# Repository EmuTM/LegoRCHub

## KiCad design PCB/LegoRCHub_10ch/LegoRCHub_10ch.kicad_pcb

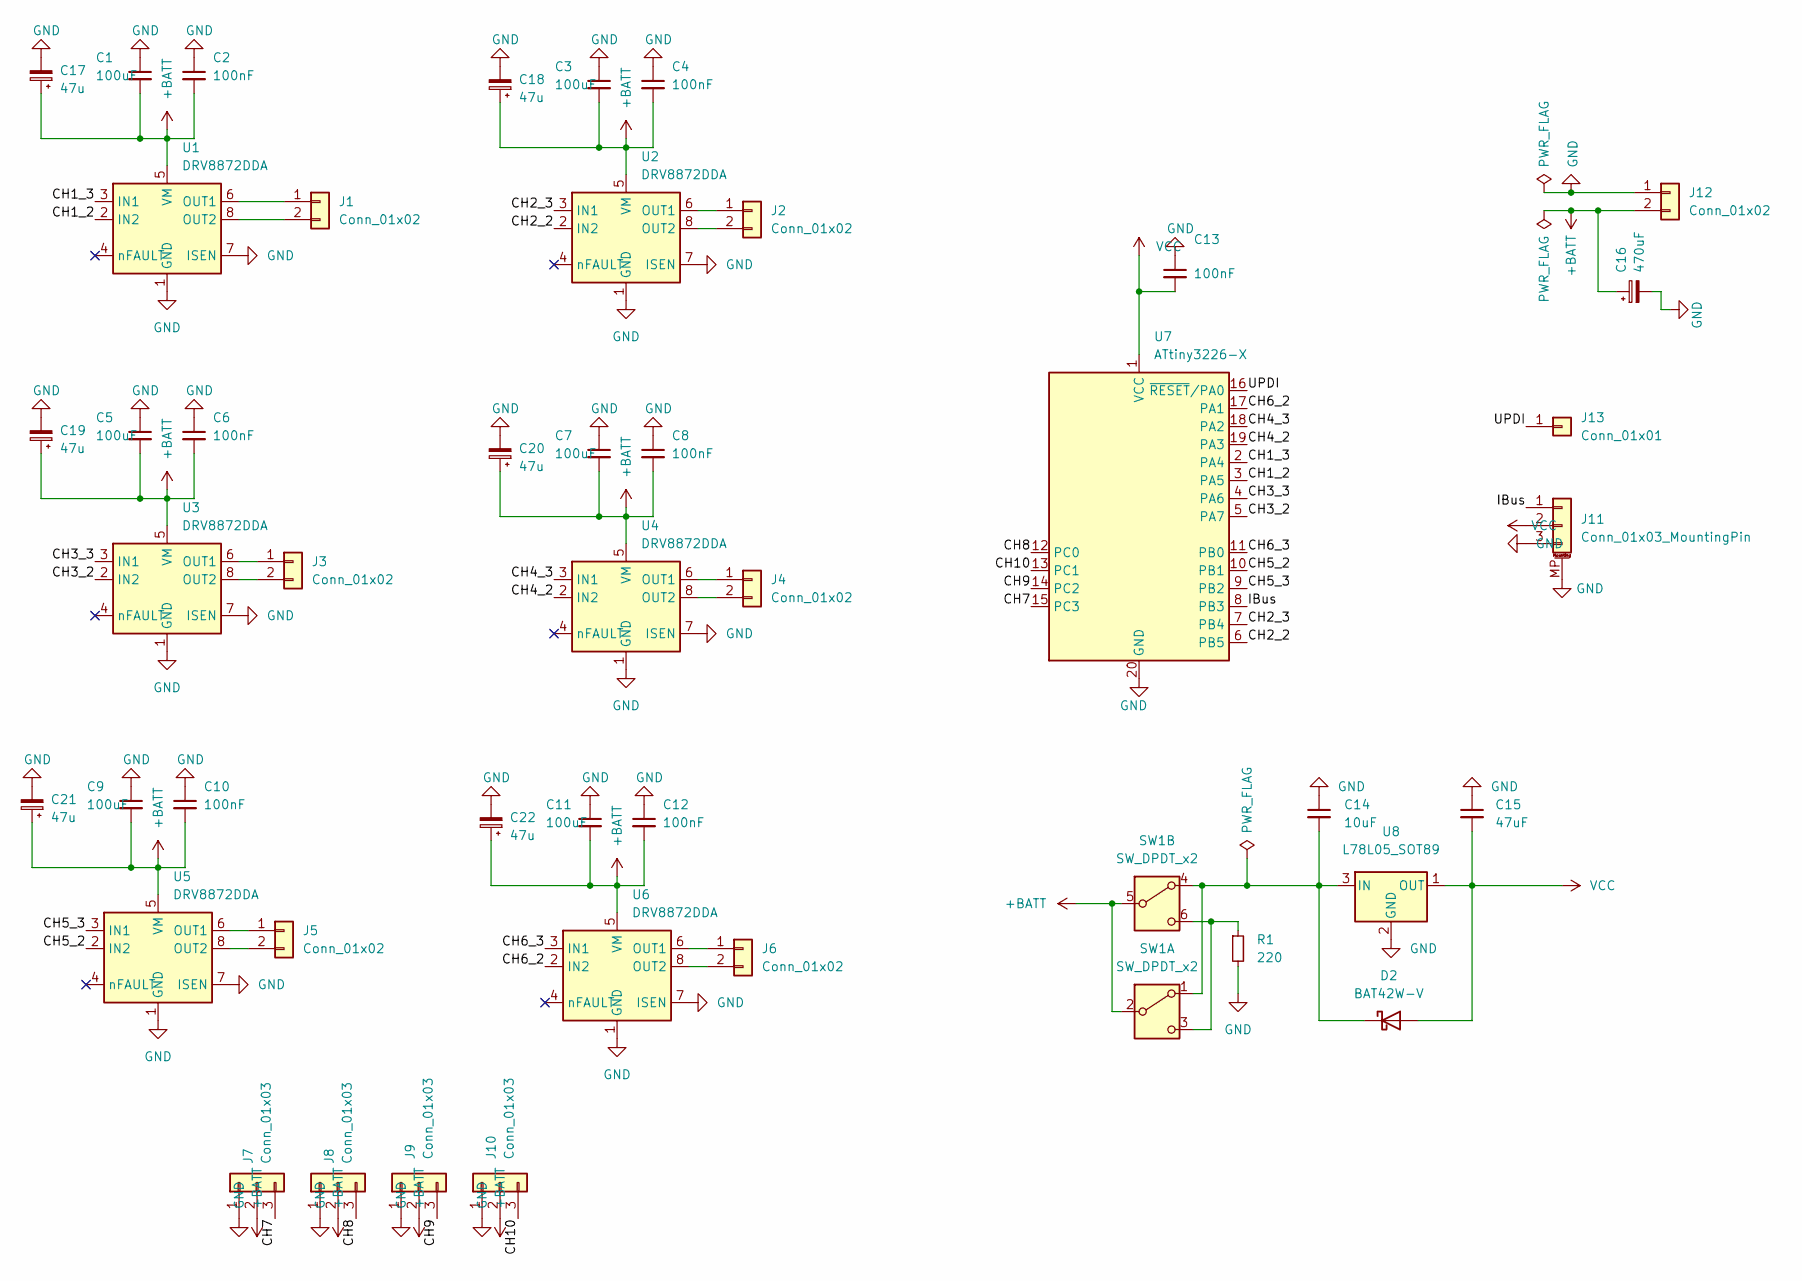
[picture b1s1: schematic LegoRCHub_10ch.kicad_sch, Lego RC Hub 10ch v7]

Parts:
C1, C3, C5, C7, C9, C11: 100uF; C_1206_3216Metric_Pad1.33x1.80mm_HandSolder
C2, C4, C6, C8, C10, C12: 100nF; C_0805_2012Metric_Pad1.18x1.45mm_HandSolder
C13: 100nF; C_1206_3216Metric_Pad1.33x1.80mm_HandSolder
C14: 10uF; C_0805_2012Metric_Pad1.18x1.45mm_HandSolder
C15: 47uF; C_0805_2012Metric_Pad1.18x1.45mm_HandSolder
C16: 470uF; CP_Elec_8x10.5
C17, C18, C19, C20, C21, C22: 47u; CP_Elec_5x5.4
D2: BAT42W-V; D_SOD-123
J1, J2, J3, J4, J5, J6: Conn_01x02; Molex_KK-254_AE-6410-02A_1x02_P2.54mm_Vertical
J7, J8, J9, J10: Conn_01x03; PinHeader_1x03_P2.54mm_Vertical
J11: Conn_01x03_MountingPin; JST_SH_BM03B-SRSS-TB_1x03-1MP_P1.00mm_Vertical
J12: Conn_01x02; AMASS_XT30U-M_1x02_P5.0mm_Vertical
J13: Conn_01x01; SolderWirePad_1x01_SMD_1x2mm
R1: 220; R_0805_2012Metric_Pad1.20x1.40mm_HandSolder
SW1: SW_DPDT_x2
U1, U2, U3, U4, U5, U6: DRV8872DDA; Texas_HTSOP-8-1EP_3.9x4.9mm_P1.27mm_EP2.95x4.9mm_Mask2.4x3.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
U7: ATtiny3226-X; SSOP-20_5.3x7.2mm_P0.65mm
U8: L78L05_SOT89; SOT-89-3

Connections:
+BATT: C1.2, C2.2, C3.2, C4.2, C5.2, C6.2, C7.2, C8.2, C9.2, C10.2, C11.2, C12.2, C16.1, C17.1, C18.1, C19.1, C20.1, C21.1, C22.1, J7.2, J8.2, J9.2, J10.2, J12.2, SW1.2 (B), SW1.5 (B), U1.5 (VM), U2.5 (VM), U3.5 (VM), U4.5 (VM), U5.5 (VM), U6.5 (VM)
/CH1_2: U1.2 (IN2), U7.3 (PA5)
/CH1_3: U1.3 (IN1), U7.2 (PA4)
/CH2_2: U2.2 (IN2), U7.6 (PB5)
/CH2_3: U2.3 (IN1), U7.7 (PB4)
/CH3_2: U3.2 (IN2), U7.5 (PA7)
/CH3_3: U3.3 (IN1), U7.4 (PA6)
/CH4_2: U4.2 (IN2), U7.19 (PA3)
/CH4_3: U4.3 (IN1), U7.18 (PA2)
/CH5_2: U5.2 (IN2), U7.10 (PB1)
/CH5_3: U5.3 (IN1), U7.9 (PB2)
/CH6_2: U6.2 (IN2), U7.17 (PA1)
/CH6_3: U6.3 (IN1), U7.11 (PB0)
/CH7: J7.3, U7.15 (PC3)
/CH8: J8.3, U7.12 (PC0)
/CH9: J9.3, U7.14 (PC2)
/CH10: J10.3, U7.13 (PC1)
/IBus: J11.1, U7.8 (PB3)
/UPDI: J13.1, U7.16 (~RESET/PA0)
GND: C1.1, C2.1, C3.1, C4.1, C5.1, C6.1, C7.1, C8.1, C9.1, C10.1, C11.1, C12.1, C13.1, C14.1, C15.1, C16.2, C17.2, C18.2, C19.2, C20.2, C21.2, C22.2, J7.1, J8.1, J9.1, J10.1, J11.3, J11.MP (MountPin), J12.1, R1.2, U1.1 (GND), U1.7 (ISEN), U1.9 (GND), U2.1 (GND), U2.7 (ISEN), U2.9 (GND), U3.1 (GND), U3.7 (ISEN), U3.9 (GND), U4.1 (GND), U4.7 (ISEN), U4.9 (GND), U5.1 (GND), U5.7 (ISEN), U5.9 (GND), U6.1 (GND), U6.7 (ISEN), U6.9 (GND), U7.20 (GND), U8.2 (GND)
unnamed: C14.2, D2.1 (K), SW1.1 (A), SW1.4 (A), U8.3 (IN)
unnamed: J1.1, U1.6 (OUT1)
unnamed: J1.2, U1.8 (OUT2)
unnamed: J2.1, U2.6 (OUT1)
unnamed: J2.2, U2.8 (OUT2)
unnamed: J3.1, U3.6 (OUT1)
unnamed: J3.2, U3.8 (OUT2)
unnamed: J4.1, U4.6 (OUT1)
unnamed: J4.2, U4.8 (OUT2)
unnamed: J5.1, U5.6 (OUT1)
unnamed: J5.2, U5.8 (OUT2)
unnamed: J6.1, U6.6 (OUT1)
unnamed: J6.2, U6.8 (OUT2)
unnamed: R1.1, SW1.3 (C), SW1.6 (C)
VCC: C13.2, C15.2, D2.2 (A), J11.2, U7.1 (VCC), U8.1 (OUT)

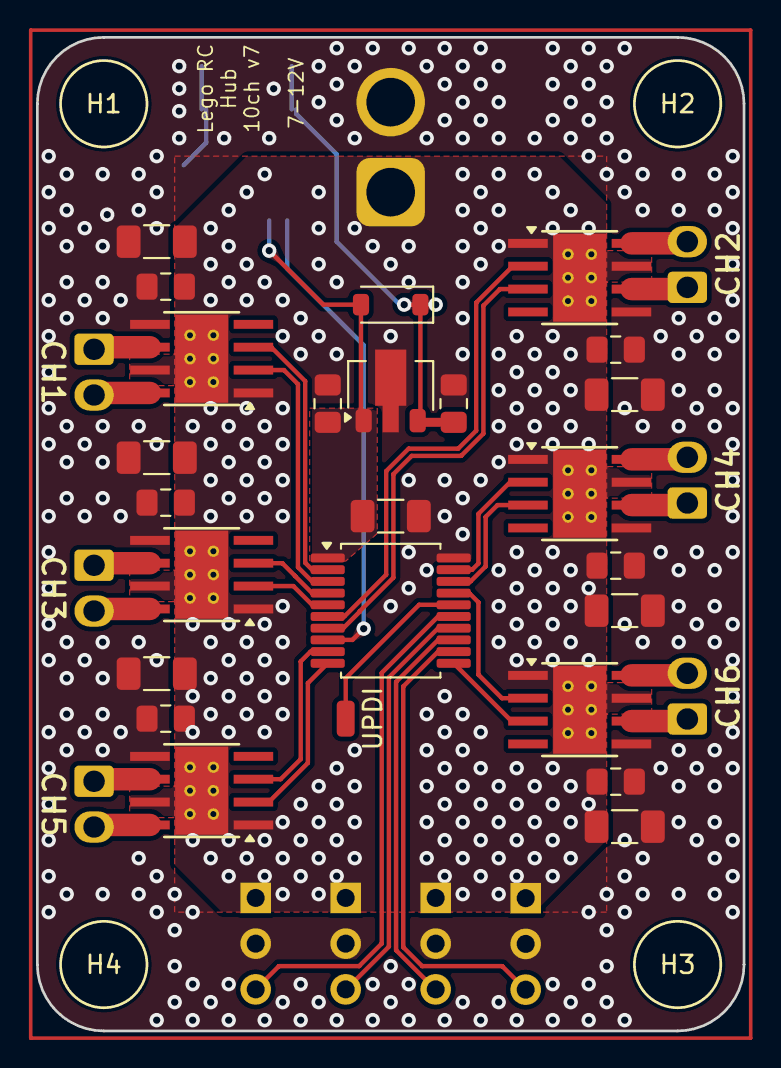
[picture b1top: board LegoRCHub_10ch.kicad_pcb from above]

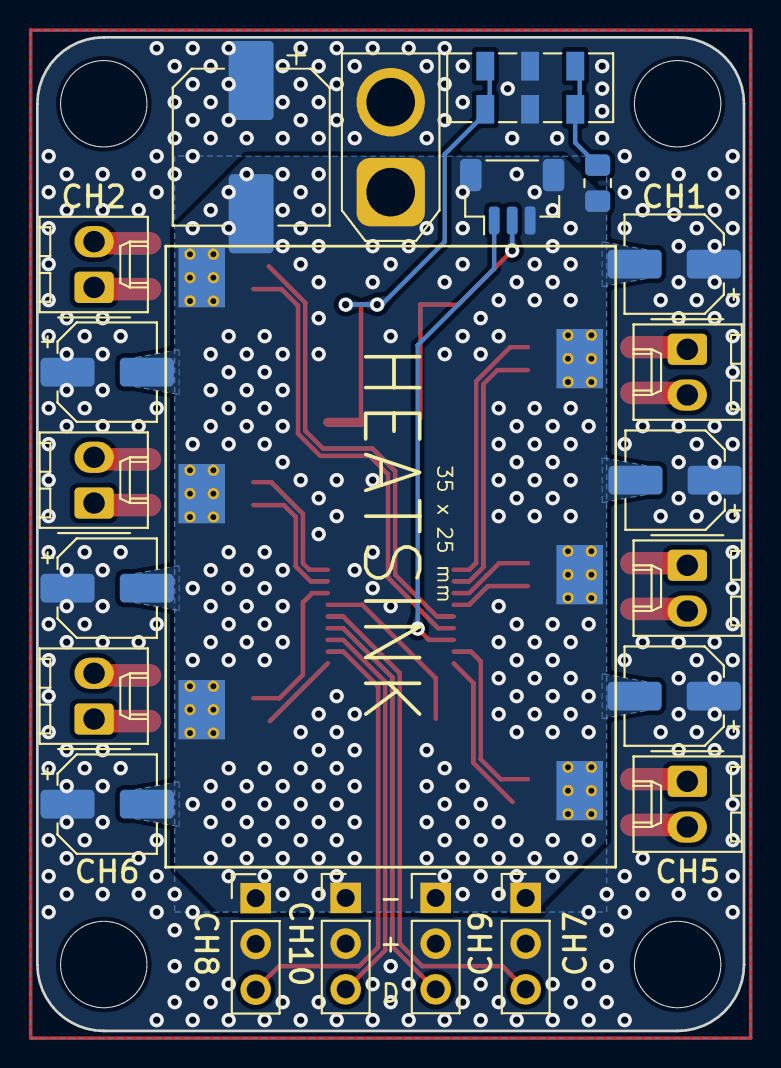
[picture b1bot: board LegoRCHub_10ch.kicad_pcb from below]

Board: 2 copper layers, 39.3 x 55.2 mm, 50 parts (21 on the bottom side), 35 nets.

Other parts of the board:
H1, H2, H3, H4: MountingHole; MountingHole_4.8mm_Lego

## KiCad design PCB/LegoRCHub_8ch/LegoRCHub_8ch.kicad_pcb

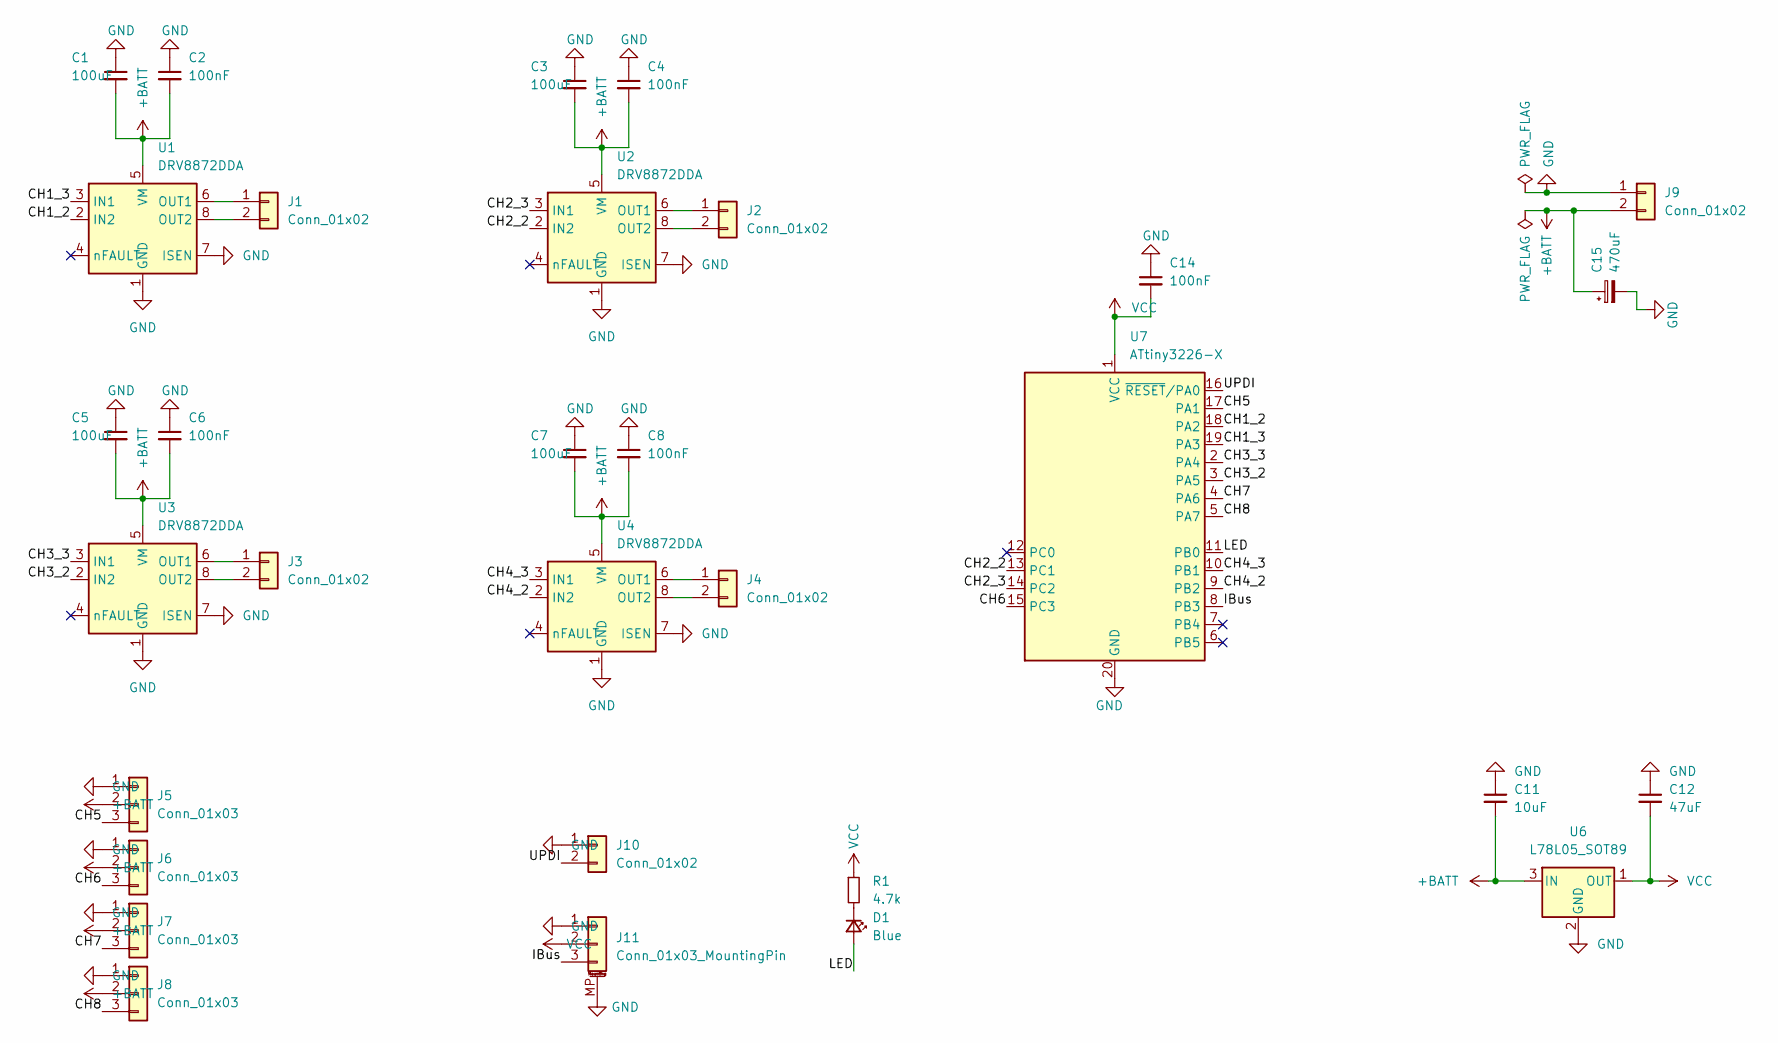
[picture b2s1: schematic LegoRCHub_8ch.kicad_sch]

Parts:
C1, C3, C5, C7: 100uF; C_1206_3216Metric_Pad1.33x1.80mm_HandSolder
C2, C4, C6, C8, C14: 100nF; C_0805_2012Metric_Pad1.18x1.45mm_HandSolder
C11: 10uF; C_0805_2012Metric_Pad1.18x1.45mm_HandSolder
C12: 47uF; C_0805_2012Metric_Pad1.18x1.45mm_HandSolder
C15: 470uF; CP_Elec_8x10.5
D1: Blue; LED_0805_2012Metric_Pad1.15x1.40mm_HandSolder
J1, J2, J3, J4: Conn_01x02; PinHeader_1x02_P2.54mm_Vertical
J5, J6, J7, J8: Conn_01x03; PinHeader_1x03_P2.54mm_Vertical
J9: Conn_01x02; AMASS_XT30U-M_1x02_P5.0mm_Vertical
J10: Conn_01x02; PinSocket_1x02_P2.54mm_Vertical
J11: Conn_01x03_MountingPin; JST_SH_BM03B-SRSS-TB_1x03-1MP_P1.00mm_Vertical
R1: 4.7k; R_0805_2012Metric_Pad1.20x1.40mm_HandSolder
U1, U2, U3, U4: DRV8872DDA; Texas_HTSOP-8-1EP_3.9x4.9mm_P1.27mm_EP2.95x4.9mm_Mask2.4x3.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
U6: L78L05_SOT89; SOT-89-3
U7: ATtiny3226-X; SSOP-20_5.3x7.2mm_P0.65mm

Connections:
+BATT: C1.2, C2.2, C3.2, C4.2, C5.2, C6.2, C7.2, C8.2, C11.2, C15.1, J5.2, J6.2, J7.2, J8.2, J9.2, U1.5 (VM), U2.5 (VM), U3.5 (VM), U4.5 (VM), U6.3 (IN)
/CH1_2: U1.2 (IN2), U7.18 (PA2)
/CH1_3: U1.3 (IN1), U7.19 (PA3)
/CH2_2: U2.2 (IN2), U7.13 (PC1)
/CH2_3: U2.3 (IN1), U7.14 (PC2)
/CH3_2: U3.2 (IN2), U7.3 (PA5)
/CH3_3: U3.3 (IN1), U7.2 (PA4)
/CH4_2: U4.2 (IN2), U7.9 (PB2)
/CH4_3: U4.3 (IN1), U7.10 (PB1)
/CH5: J5.3, U7.17 (PA1)
/CH6: J6.3, U7.15 (PC3)
/CH7: J7.3, U7.4 (PA6)
/CH8: J8.3, U7.5 (PA7)
/IBus: J11.3, U7.8 (PB3)
/LED: D1.2 (A), U7.11 (PB0)
/UPDI: J10.2, U7.16 (~RESET/PA0)
GND: C1.1, C2.1, C3.1, C4.1, C5.1, C6.1, C7.1, C8.1, C11.1, C12.1, C14.1, C15.2, J5.1, J6.1, J7.1, J8.1, J9.1, J10.1, J11.1, J11.MP (MountPin), U1.1 (GND), U1.7 (ISEN), U1.9 (GND), U2.1 (GND), U2.7 (ISEN), U2.9 (GND), U3.1 (GND), U3.7 (ISEN), U3.9 (GND), U4.1 (GND), U4.7 (ISEN), U4.9 (GND), U6.2 (GND), U7.20 (GND)
unnamed: D1.1 (K), R1.2
unnamed: J1.1, U1.6 (OUT1)
unnamed: J1.2, U1.8 (OUT2)
unnamed: J2.1, U2.6 (OUT1)
unnamed: J2.2, U2.8 (OUT2)
unnamed: J3.1, U3.6 (OUT1)
unnamed: J3.2, U3.8 (OUT2)
unnamed: J4.1, U4.6 (OUT1)
unnamed: J4.2, U4.8 (OUT2)
VCC: C12.2, C14.2, J11.2, R1.1, U6.1 (OUT), U7.1 (VCC)

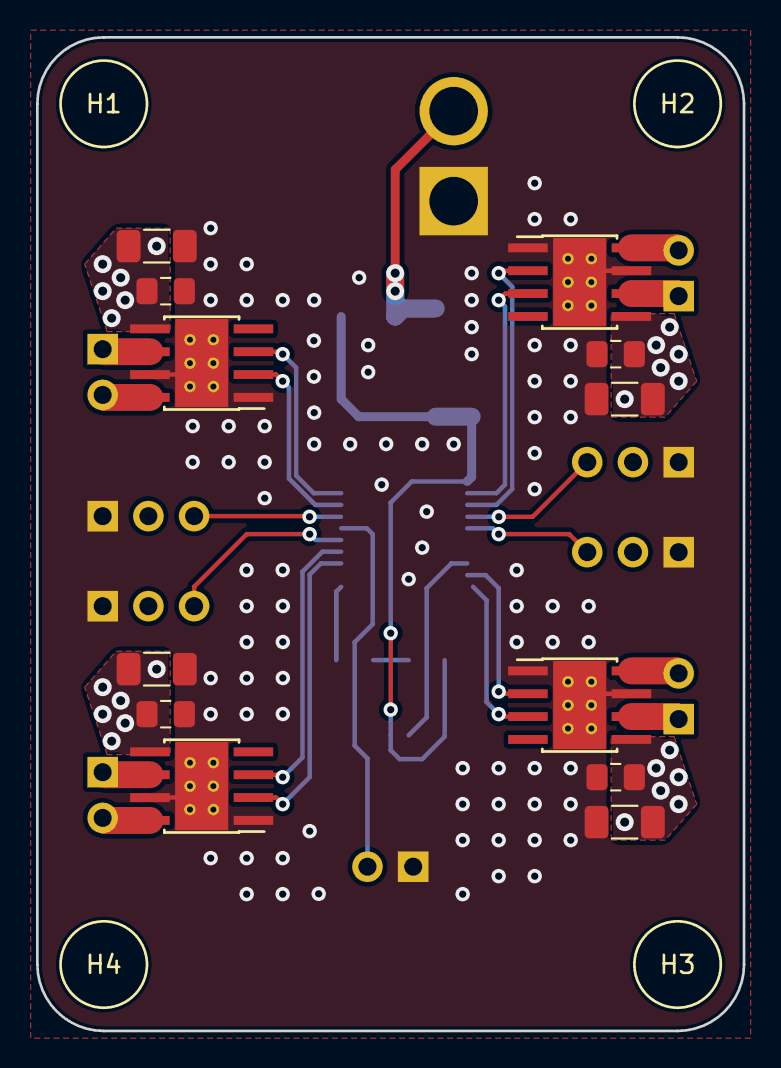
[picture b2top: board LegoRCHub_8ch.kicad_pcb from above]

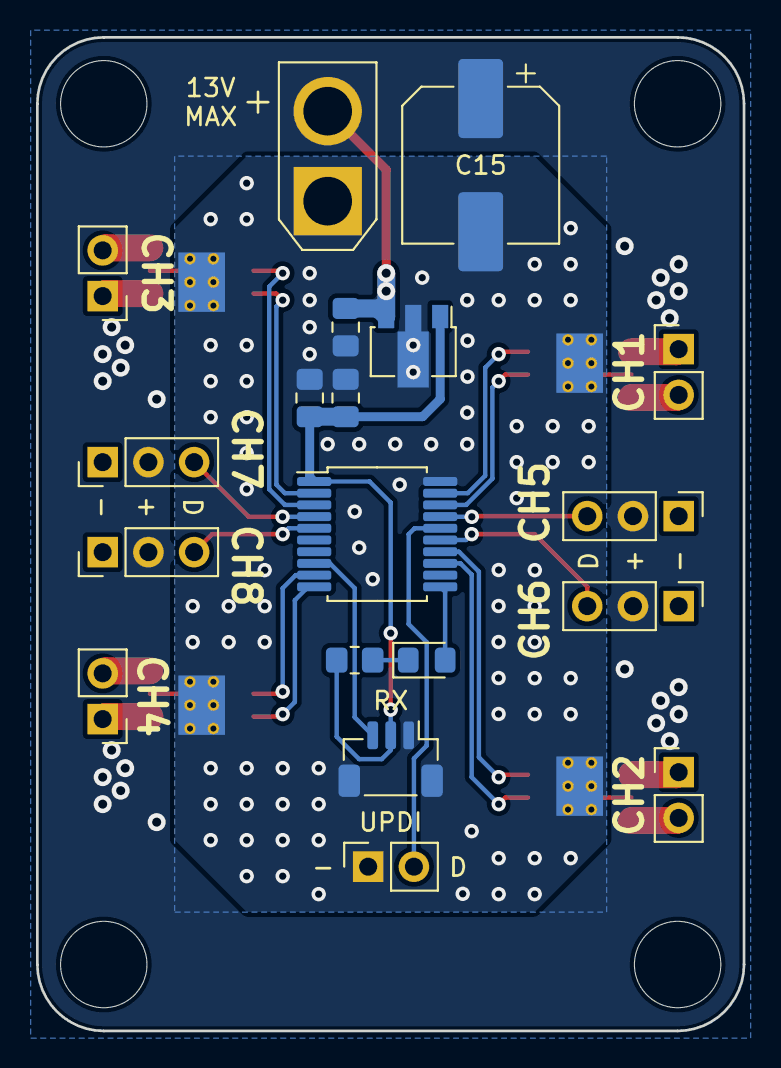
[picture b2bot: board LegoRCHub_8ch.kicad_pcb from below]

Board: 2 copper layers, 39.3 x 55.2 mm, 35 parts (19 on the bottom side), 27 nets.

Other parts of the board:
H1, H2, H3, H4: MountingHole; MountingHole_4.8mm_Lego

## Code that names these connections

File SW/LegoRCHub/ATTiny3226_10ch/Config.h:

#ifndef _CONFIG_h
#define _CONFIG_h


typedef struct PWMPin
{
	PORT_t* port;
	uint8_t bitMask;
	uint8_t dutyCycle;
} pwmPin_t;


//IMPORTANT NOTE: this resolution is interdependant on timer A settings and should not be changed per se
#define PWM_RESOLUTION 31

#define MIN_PWM 7
#define MAX_PWM 32 //+1 for constant on

//use this for braking effect; both pins 1 when idle
//#define PWM_SLOW_DECAY


//IMPORTANT NOTE: maps pwm channels to pins that drive H bridges
//THIS IS PCB DESIGN DEPENDANT!
pwmPin_t pwmPins[6 * 2]
{
	{&PORTA, digitalPinToBitMask(PIN_PA5)}, //ch0_up (ch1_2)
	{&PORTA, digitalPinToBitMask(PIN_PA4)}, //ch0_down (ch1_3)

	{&PORTB, digitalPinToBitMask(PIN_PB5)}, //ch1_up (ch2_2)
	{&PORTB, digitalPinToBitMask(PIN_PB4)}, //ch1_down (ch2_3)

	{&PORTA, digitalPinToBitMask(PIN_PA7)}, //ch2_up (ch3_2)
	{&PORTA, digitalPinToBitMask(PIN_PA6)}, //ch2_down (ch3_3)

	{&PORTA, digitalPinToBitMask(PIN_PA3)}, //ch3_up (ch4_2)
	{&PORTA, digitalPinToBitMask(PIN_PA2)}, //ch3_down (ch4_3)

	{&PORTB, digitalPinToBitMask(PIN_PB1)}, //ch4_up (ch5_2)
	{&PORTB, digitalPinToBitMask(PIN_PB2)}, //ch4_down (ch5_3)

	{&PORTA, digitalPinToBitMask(PIN_PA1)}, //ch5_up (ch6_2)
	{&PORTB, digitalPinToBitMask(PIN_PB0)}  //ch5_down (ch6_3)
};
const uint8_t pwmPinsCount = sizeof(pwmPins) / sizeof(pwmPins[0]);

#include <Servo_megaTinyCore.h>

typedef struct ServoPin
{
	uint8_t pin;
	Servo servo;

	static inline void attachAll(ServoPin* pins, const uint8_t pinCount)
	{
		for (int a = 0; a < pinCount; a++)
		{
			pins[a].servo.attach(pins[a].pin);
		}
	}

} servoPin_t;

#define SERVO_MIN 0
#define SERVO_MAX 180

//IMPORTANT NOTE: maps servo channels to pins that drive servos
//THIS IS PCB DESIGN DEPENDANT!
#ifdef DEBUG
const servoPin_t servoPins[3]
{
	//{PIN_PC3, Servo()}, //pin reserved for debug!
	{PIN_PC0, Servo()}, //ch8
	{PIN_PC2, Servo()}, //ch9
	{PIN_PC1, Servo()} //ch10
};
#else
const servoPin_t servoPins[4]
{
	{PIN_PC3, Servo()}, //ch7
	{PIN_PC0, Servo()}, //ch8
	{PIN_PC2, Servo()}, //ch9
	{PIN_PC1, Servo()} //ch10
};
#endif
const uint8_t servoPinsCount = sizeof(servoPins) / sizeof(servoPins[0]);

#include "IBus.h"

//USE THIS TO MAP IBUS SIGNALS TO OUTPUT CHANNELS
//number in here define the pwm/servo channel (channels 0-5 are pwm; channels 6-9 are servos) with respect to iBus channel
uint8_t iBusMap[IBUS_CHANNEL_COUNT]
{
	0,
	1,
	2,
	3,
	4,
	5,
	6,
	7,
	8,
	9,


	10, //do not use - no pin available
	11, //do not use - no pin available
	12, //do not use - no pin available
	13  //do not use - no pin available
};

#endif

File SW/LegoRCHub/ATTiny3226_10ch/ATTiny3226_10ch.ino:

#define VERSION 6


//#define DEBUG
#ifdef DEBUG
#define SW_SERIAL_BAUD_RATE 9600

//enable this to measure PWM frequency
//#define DEBUG_ISR_FREQ
#endif


#ifdef DEBUG
#include <SoftwareSerial.h>

#endif
#include "IBus.h"
#include "Config.h"
#include <Servo_megaTinyCore.h>


#ifdef DEBUG
SoftwareSerial mySerial(-1 /*rx not supported*/, PIN_PC3 /*any pin except UPDI*/);
IBus iBus(&Serial, &mySerial);

#ifdef DEBUG_ISR_FREQ
volatile uint32_t isrCounter = 0; //counter for ISR calls
volatile uint32_t lastMillis = 0; //stores last millis for frequency calculation
#endif
#else
IBus iBus(&Serial);
#endif


//state
volatile pwmPin_t* drivenPins[6]
{
	&pwmPins[0],
	&pwmPins[2],
	&pwmPins[4],
	&pwmPins[6],
	&pwmPins[8],
	&pwmPins[10]
};

volatile uint16_t previousVals[10] = { 0, 0, 0, 0, 0, 0, 0, 0, 0, 0 };
//state


void setup()
{
#ifdef DEBUG
	delay(3000); //this is for visual convenience when using port monitors
	mySerial.begin(SW_SERIAL_BAUD_RATE);
	mySerial.print("DEBUG (v");
	mySerial.print(VERSION);
	mySerial.println(")");
#endif

	noInterrupts();

	iBus.begin();

	//disable TX in the USART peripheral, so the tx pin is available (for pwm)
	USART0.CTRLB &= ~USART_TXEN_bm;

	//configure all pins on PORTA and PORTB as output (for pwm)
	PORTA.DIRSET = 0xfe; //PA0 is UPDI
	PORTB.DIRSET = 0x37; //PB3 is RX

	//set ISR on timer A
	{
		//timer_frequency_Hz = processor_clock_frequency_Hz / prescaler_value
		//interrupt_frequency_Hz = timer_frequency_Hz / (TCA0.SINGLE.PER[timer period] + 1)
		//pwm_frequency_Hz = timer_frequency_Hz / resolution

		//3kHz with PWM_RESOLUTION being 31
		TCA0.SINGLE.CTRLA = TCA_SINGLE_CLKSEL_enum::TCA_SINGLE_CLKSEL_DIV16_gc | TCA_SINGLE_ENABLE_bm;
		TCA0.SINGLE.PER = 12;
		TCA0.SINGLE.INTCTRL = TCA_SINGLE_OVF_bm; //enable overflow interrupt
	}

	//attach servos
	ServoPin::attachAll(servoPins, servoPinsCount);

	interrupts();


}

void loop()
{
#ifdef DEBUG_ISR_FREQ
	noInterrupts(); //disable interrupts to safely access shared variables
	uint32_t count = isrCounter;
	uint32_t lastUpdate = lastMillis;
	interrupts(); //re-enable interrupts

	//calculate the ISR frequency once every second
	if (millis() - lastUpdate >= 1000)
	{
		noInterrupts();

		//update the lastMillis timestamp
		lastMillis = millis();
		//reset the ISR counter
		isrCounter = 0;

		interrupts();

		mySerial.print("ISR Frequency: ");
		mySerial.print(count);
		mySerial.println(" Hz");
	}
#else
	if (iBus.loop())
	{
#ifdef DEBUG
		for (int a = 0; a < IBUS_CHANNEL_COUNT; a++)
		{
			mySerial.print(iBus.channels[iBusMap[a]]);
			mySerial.print(";");
		}
		mySerial.println();
#endif

		//first 6 channels are pwm pins (6 x H-bridge; 2 pins per bridge, alternately driven)
		for (int a = 0; a < 6; a++)
		{
			int _2a = 2 * a;
			int _2a1 = _2a + 1;

			uint16_t val = iBus.channels[iBusMap[a]];

			if (val != previousVals[a])
			{
				previousVals[a] = val;

				if (val > IBUS_MID)
				{
#ifdef DEBUG
					mySerial.print("CH ");
					mySerial.print(a);
					mySerial.print(" UP:");
					mySerial.println(map(val, IBUS_MID, IBUS_MAX, MIN_PWM, MAX_PWM));
#endif

					//make sure to switch the proper pin in the drivenPins
					if (drivenPins[a] != &pwmPins[_2a])
					{
						drivenPins[a] = &pwmPins[_2a];
					}

					//set the duty cycle on the driven pin...
					drivenPins[a]->dutyCycle = map(val, IBUS_MID, IBUS_MAX, MIN_PWM, MAX_PWM);

					//...and DRIVE the other pin
					pwmPins[_2a1].port->OUTCLR = pwmPins[_2a1].bitMask;
				}
				else if (val < IBUS_MID)
				{
#ifdef DEBUG
					mySerial.print("CH ");
					mySerial.print(a);
					mySerial.print(" DOWN:");
					mySerial.println(map(val, IBUS_MID, IBUS_MIN, MIN_PWM, MAX_PWM));
#endif

					//make sure to switch the proper pin in the drivenPins
					if (drivenPins[a] != &pwmPins[_2a1])
					{
						drivenPins[a] = &pwmPins[_2a1];
					}

					//set the duty cycle on the driven pin...
					drivenPins[a]->dutyCycle = map(val, IBUS_MID, IBUS_MIN, MIN_PWM, MAX_PWM);

					//...and DRIVE the other pin
					pwmPins[_2a].port->OUTCLR = pwmPins[_2a].bitMask;
				}
				else
				{
#ifdef DEBUG
					mySerial.print("CH ");
					mySerial.print(a);
					mySerial.println("MID");
#endif

					//both pins must be OFF; set the duty cycle, but also drive the pins
#ifdef PWM_SLOW_DECAY
					drivenPins[a]->dutyCycle = MAX_PWM;

					pwmPins[_2a].port->OUTSET = pwmPins[_2a].bitMask;
					pwmPins[_2a1].port->OUTSET = pwmPins[_2a1].bitMask;
#else
					drivenPins[a]->dutyCycle = 0;

					pwmPins[_2a].port->OUTCLR = pwmPins[_2a].bitMask;
					pwmPins[_2a1].port->OUTCLR = pwmPins[_2a1].bitMask;
#endif
				}
			}
		}


#ifdef DEBUG
		for (int a = 0; a < pwmPinsCount; a += 2)
		{
			mySerial.print("CH ");
			mySerial.print(a / 2);
			mySerial.print(" : ");
			mySerial.print(pwmPins[a]->dutyCycle);
			mySerial.print(" / ");
			mySerial.print(pwmPins[a + 1]->dutyCycle);
			mySerial.println();
		}
#endif

		//next 4 channels go to servo pins
		for (int a = 0; a < servoPinsCount; a++)
		{
			uint16_t val = iBus.channels[iBusMap[a + 6]];

			if (val != previousVals[a + 6])
			{
				previousVals[a + 6] = val;
				servoPins[a].servo.write(map(val, IBUS_MIN, IBUS_MAX, SERVO_MIN, SERVO_MAX));
			}
		}
	}
#endif
}

//SW PWM ISR
ISR(TCA0_OVF_vect)
{
	static uint8_t currentPwm = 0;


	if (currentPwm < drivenPins[0]->dutyCycle)
	{
		drivenPins[0]->port->OUTSET = drivenPins[0]->bitMask; //set pin high
	}
	else
	{
		drivenPins[0]->port->OUTCLR = drivenPins[0]->bitMask; //set pin low
	}

	if (currentPwm < drivenPins[1]->dutyCycle)
	{
		drivenPins[1]->port->OUTSET = drivenPins[1]->bitMask; //set pin high
	}
	else
	{
		drivenPins[1]->port->OUTCLR = drivenPins[1]->bitMask; //set pin low
	}

	if (currentPwm < drivenPins[2]->dutyCycle)
	{
		drivenPins[2]->port->OUTSET = drivenPins[2]->bitMask; //set pin high
	}
	else
	{
		drivenPins[2]->port->OUTCLR = drivenPins[2]->bitMask; //set pin low
	}

	if (currentPwm < drivenPins[3]->dutyCycle)
	{
		drivenPins[3]->port->OUTSET = drivenPins[3]->bitMask; //set pin high
	}
	else
	{
		drivenPins[3]->port->OUTCLR = drivenPins[3]->bitMask; //set pin low
	}

	if (currentPwm < drivenPins[4]->dutyCycle)
	{
		drivenPins[4]->port->OUTSET = drivenPins[4]->bitMask; //set pin high
	}
	else
	{
		drivenPins[4]->port->OUTCLR = drivenPins[4]->bitMask; //set pin low
	}

	if (currentPwm < drivenPins[5]->dutyCycle)
	{
		drivenPins[5]->port->OUTSET = drivenPins[5]->bitMask; //set pin high
	}
	else
	{
		drivenPins[5]->port->OUTCLR = drivenPins[5]->bitMask; //set pin low
	}

	//increases or resets currentPwm; this is a trickery, from chatgpt, like modulo but faster
	currentPwm = (currentPwm + 1) & PWM_RESOLUTION;

	//clear the interrupt flag
	TCA0.SINGLE.INTFLAGS = TCA_SINGLE_OVF_bm;
}

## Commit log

2024-12-19 First. Added .gitignore file
2024-12-19 Added Models together with first model: PCB model for Lego Frame 5x7
2024-12-19 Added LegoRCHub_8ch project (KiCad)
2024-12-19 Updated PCB/.gitignore so it ignores ".kicad_prl" files (stores current user settings)
2024-12-19 LegoRCHub_8ch: added schematic
2024-12-19 PCB: added "CustomFootprints" together with Lego mounting hole (4.8mm)
2024-12-19 LegoRCHub_8ch: working on pcb design...
2024-12-20 LegoRCHub_8ch: finished PCB (beta 1)
2024-12-22 LegoRCHub_8ch: finished PCB (beta 2)
2024-12-22 LegoRCHub_8ch: finished PCB (beta 3)
2024-12-23 LegoRCHub_8ch_ServoVoltageConversion: working on pcb design...
2024-12-29 LegoRCHub_8ch: finished PCB (beta 4)
2024-12-31 LegoRCHub_8ch: finished PCB (beta 5)
2025-01-02 LegoRCHub_8ch: finished PCB (beta 6)
2025-01-02 LegoRCHub_8ch: beta 6: simplified design with 4/4 layout
2025-01-02 LegoRCHub_8ch: beta 7
2025-01-04 LegoRCHub_8ch: beta 8 (layout somewhat finished)
2025-01-04 Added project LegoRCHub_10ch: (beta 1)
2025-01-17 Added project LegoRCHub_10ch: (beta 2): changed pins to screw terminals
2025-01-21 LegoRCHub_10ch: ...
2025-01-21 LegoRCHub_10ch: ...
    Revert "LegoRCHub_10ch: ..."
    This reverts commit a8209f8826470efcec7313ecef0b47345458ad62.
2025-01-22 LegoRCHub_10ch: improved design - beta 1
2025-01-23 LegoRCHub_10ch: drv8872s motor traces width decreased to allow for a width increase on isen pin
2025-01-23 LegoRCHub_10ch: improved layout...
2025-01-24 LegoRCHub_10ch: improved layout: beta-2
2025-01-24 LegoRCHub_10ch: improved layout: beta-3
2025-01-24 Lego RC Hub 10ch v1
2025-01-24 Added "SW" together with first project ATTiny3226_10ch (it works)
2025-01-25 SW ATTiny3226_10ch: version 1; compliant with pcb design. tested on protoboard; to be tested in real world scenario
2025-02-15 Lego RC Hub 10ch: converted to KiCad8
2025-02-15 Lego RC Hub 10ch v2: fully migrated to KiCad8
2025-02-21 Lego RC Hub 10ch v3: improved zones
2025-02-21 Lego RC Hub 10ch: fully migrated to KiCad9
2025-02-21 Lego RC Hub 10ch: v4
2025-02-22 Lego RC Hub 8ch DISCARDED
2025-02-22 Lego RC Hub 10ch: minor tweaking for better rule compliance
2025-02-23 Lego RC Hub 10ch: v5: added additional capacitors on channels + remade all vias
2025-03-01 SW ATTiny3226_10ch v2: added tolerance to ibus channels
2025-03-19 SW ATTiny3226_10ch v3: traded PWM resolution for frequency for easier starting of motors
2025-03-30 Minor changes that do no alter the functionality
2025-03-31 Increased PWM frequency
2025-03-31 Simplified pin definitions and improved PWM frequency again (3kHz)
2025-04-03 Small improvements and code clean up-s
2025-04-03 SW v4
2025-04-06 SW v5: little improvements and refactoring
2025-05-08 SW v6: IBUS_MID_TOLERANCE 25
2025-05-08 PCB v6: inverted connector (as it should be)
2025-07-07 PCB: working on double CPU design...
2026-02-22 PCB v7: added switch for microprocessor on/off
